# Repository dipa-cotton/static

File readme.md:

# static
custom FM Radio, with a SX1278 for LoRA capabilities!

## project overview
this FM radio contains a RDA5807, TDA2822, an infrared sensor, and a SX1278. these are the main components, and along with a 0.96 inch OLED display, a microSD card module, and more, this project is versatile and can both play audio as well as function as an FM radio, along with LORA capabilities.

## pictures

There was no CAD Case built for this project, so the case can be built later on once the antenna and potentiometer + button placement can be visualized. (I haven't decided on the button placement for this project yet, so I don't want to constrain placement just yet. Once it is assembled, a case will be built.)

## BOM Overview
- 3 10K ohm resistor
- 1 100 ohm resistor
- 5 polarized capacitors
- 1 4.7 µF decoupling capacitor
- 3 100nF capacitors
- 1 10nF capacitor
- 2 10pf capacitors
- 1 PJ-3200
- 1 0.96in OLED Display
- 1 MicroSD Card Module
- 2 speakers
- 2 potentiometers
- 4 push buttons
- 1 XIAO rp2040 microcontroller
- 1 RDA5807
- 1 TDA2822
- 1 TSOP38238
- 1 SX1278
- 1 32 MHz Crystal
### Overall cost: (including shipping and PCB) is $58

a more detailed list can be found in BOM.csv :)

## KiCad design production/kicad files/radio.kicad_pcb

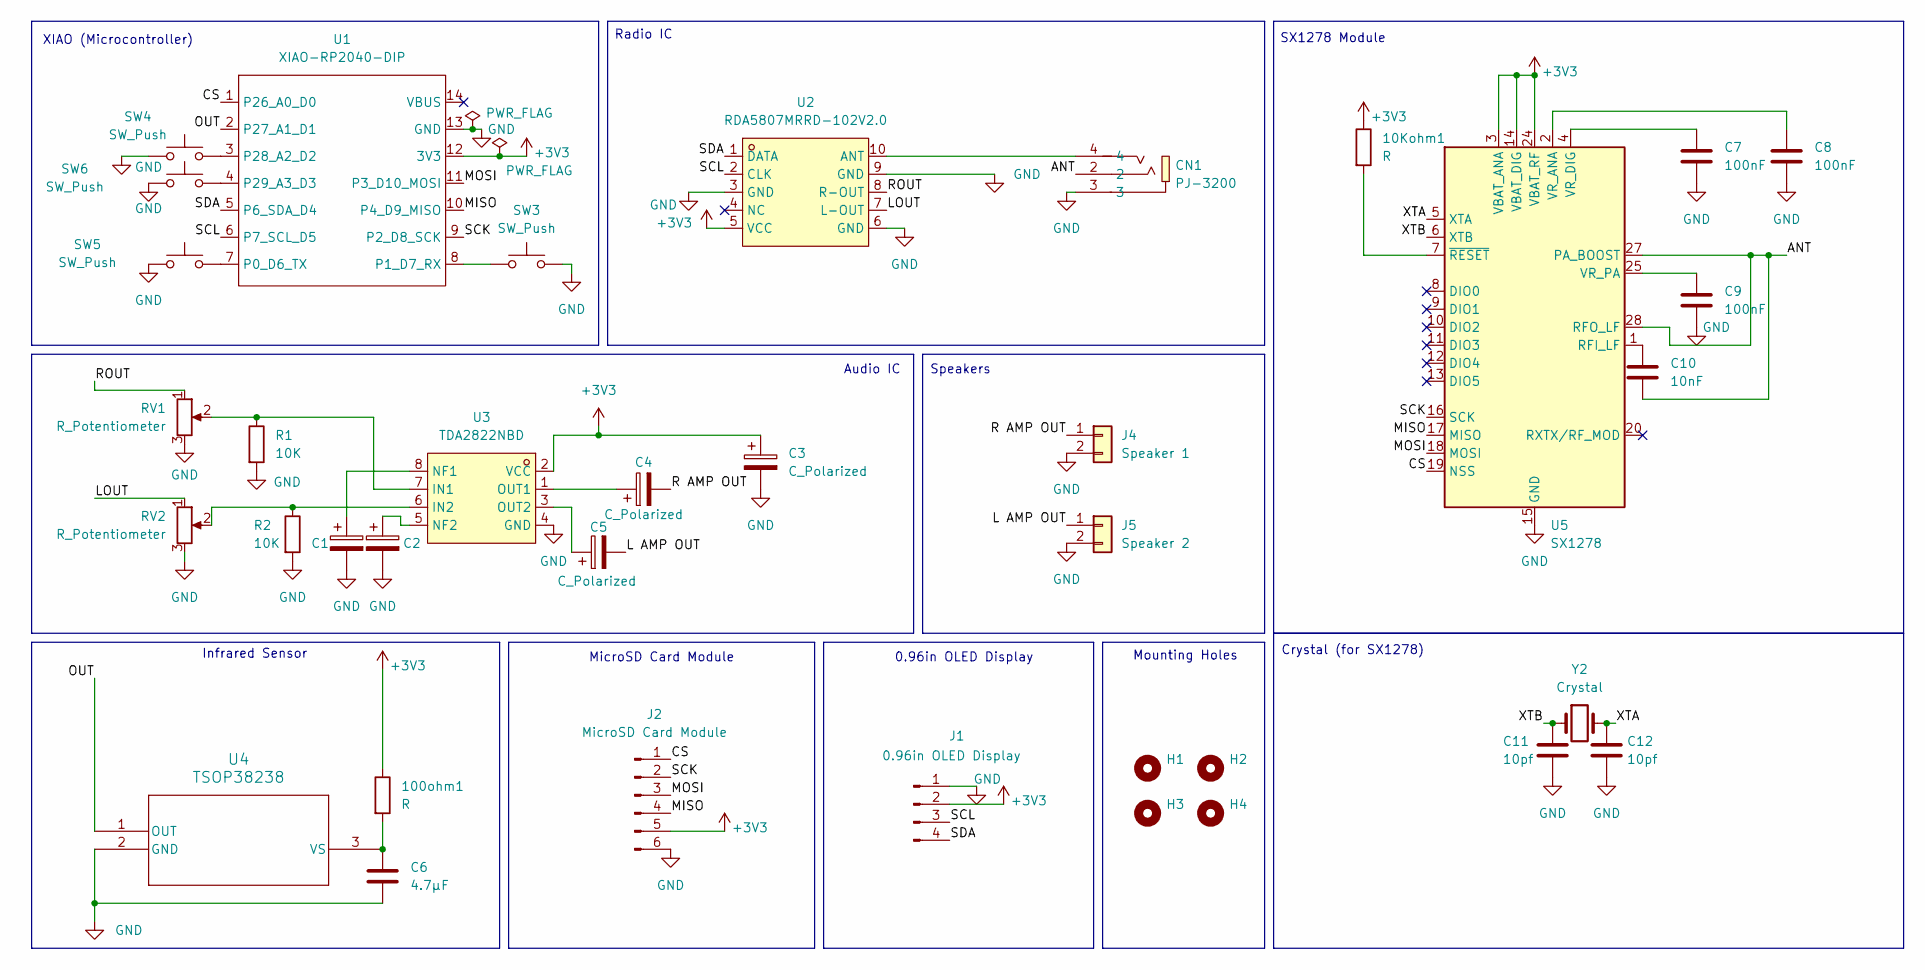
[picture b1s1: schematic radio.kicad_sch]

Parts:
10Kohm1, 100ohm1: R; R_Axial_DIN0204_L3.6mm_D1.6mm_P7.62mm_Horizontal
C1, C2, C3, C4, C5: C_Polarized; CP_Radial_D6.3mm_P2.50mm
C6: 4.7µF; R_Axial_DIN0204_L3.6mm_D1.6mm_P1.90mm_Vertical
C7, C8, C9: 100nF; R_Axial_DIN0204_L3.6mm_D1.6mm_P1.90mm_Vertical
C10: 10nF; R_Axial_DIN0204_L3.6mm_D1.6mm_P1.90mm_Vertical
C11, C12: 10pf; R_Axial_DIN0204_L3.6mm_D1.6mm_P1.90mm_Vertical
CN1: PJ-3200; AUDIO-TH_PJ-3200; MPN PJ-3200; LCSC Part C2689690
H1, H2, H3, H4: MountingHole; MountingHole_2.7mm_M2.5
J1: 0.96in OLED Display; PinHeader_1x04_P2.54mm_Vertical
J2: MicroSD Card Module; PinHeader_1x06_P2.54mm_Vertical
J4: Speaker 1; PinHeader_1x02_P2.54mm_Vertical
J5: Speaker 2; PinHeader_1x02_P2.54mm_Vertical
R1, R2: 10K; R_Axial_DIN0207_L6.3mm_D2.5mm_P7.62mm_Horizontal
RV1, RV2: R_Potentiometer; PinHeader_1x03_P2.54mm_Vertical
SW3, SW4, SW5, SW6: SW_Push; PinHeader_1x02_P2.54mm_Vertical
U1: XIAO-RP2040-DIP
U2: RDA5807MRRD-102V2.0; RDA5807; MPN RDA5807MRRD-102V2.0; LCSC Part C9900205627
U3: TDA2822NBD; DIP-8_W7.62mm; MPN TDA2822NBD; LCSC Part C51927337
U4: TSOP38238; TSOP382
U5: SX1278; QFN-28-1EP_6x6mm_P0.65mm_EP4.8x4.8mm
Y2: Crystal; Crystal_AT310_D3.0mm_L10.0mm_Horizontal

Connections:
+3V3: 10Kohm1.1, 100ohm1.1, C3.1, J1.2, J2.5, U1.12 (3V3), U2.5 (VCC), U3.2 (VCC), U5.3 (VBAT_ANA), U5.14 (VBAT_DIG), U5.24 (VBAT_RF)
/ANT: C10.2, CN1.2, U5.27 (PA_BOOST), U5.28 (RFO_LF)
/CS: J2.1, U1.1 (P26_A0_D0), U5.19 (NSS)
/L AMP OUT: C5.2, J5.1
/LOUT: RV2.1, U2.7 (L-OUT)
/MISO: J2.4, U1.10 (P4_D9_MISO), U5.17 (MISO)
/MOSI: J2.3, U1.11 (P3_D10_MOSI), U5.18 (MOSI)
/OUT: U1.2 (P27_A1_D1), U4.1 (OUT)
/R AMP OUT: C4.2, J4.1
/ROUT: RV1.1, U2.8 (R-OUT)
/SCK: J2.2, U1.9 (P2_D8_SCK), U5.16 (SCK)
/SCL: J1.3, U1.6 (P7_SCL_D5), U2.2 (CLK)
/SDA: J1.4, U1.5 (P6_SDA_D4), U2.1 (DATA)
/XTA: C12.1, U5.5 (XTA), Y2.2
/XTB: C11.1, U5.6 (XTB), Y2.1
GND: C1.2, C2.2, C3.2, C6.2, C7.2, C8.2, C9.2, C11.2, C12.2, CN1.3, J1.1, J2.6, J4.2, J5.2, R1.2, R2.2, RV1.3, RV2.3, SW3.2, SW4.1, SW5.1, SW6.1, U1.13 (GND), U2.3 (GND), U2.6 (GND), U2.9 (GND), U3.4 (GND), U4.2 (GND), U5.15 (GND), U5.21 (GND), U5.22 (GND), U5.23 (GND), U5.26 (GND), U5.29 (GND)
unnamed: SW5.2, U1.7 (P0_D6_TX)
unnamed: SW3.1, U1.8 (P1_D7_RX)
unnamed: SW4.2, U1.3 (P28_A2_D2)
unnamed: SW6.2, U1.4 (P29_A3_D3)
unnamed: CN1.4, U2.10 (ANT)
unnamed: R1.1, RV1.2, U3.7 (IN1)
unnamed: R2.1, RV2.2, U3.6 (IN2)
unnamed: C1.1, U3.8 (NF1)
unnamed: C2.1, U3.5 (NF2)
unnamed: C4.1, U3.1 (OUT1)
unnamed: C5.1, U3.3 (OUT2)
unnamed: 100ohm1.2, C6.1, U4.3 (VS)
unnamed: C10.1, U5.1 (RFI_LF)
unnamed: C8.1, U5.2 (VR_ANA)
unnamed: C7.1, U5.4 (VR_DIG)
unnamed: C9.1, U5.25 (VR_PA)
unnamed: 10Kohm1.2, U5.7 (~RESET)

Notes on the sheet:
MicroSD Card Module
SX1278 Module
Audio IC
Infrared Sensor
Mounting Holes
Radio IC
XIAO (Microcontroller)
Crystal (for SX1278)
0.96in OLED Display
Speakers

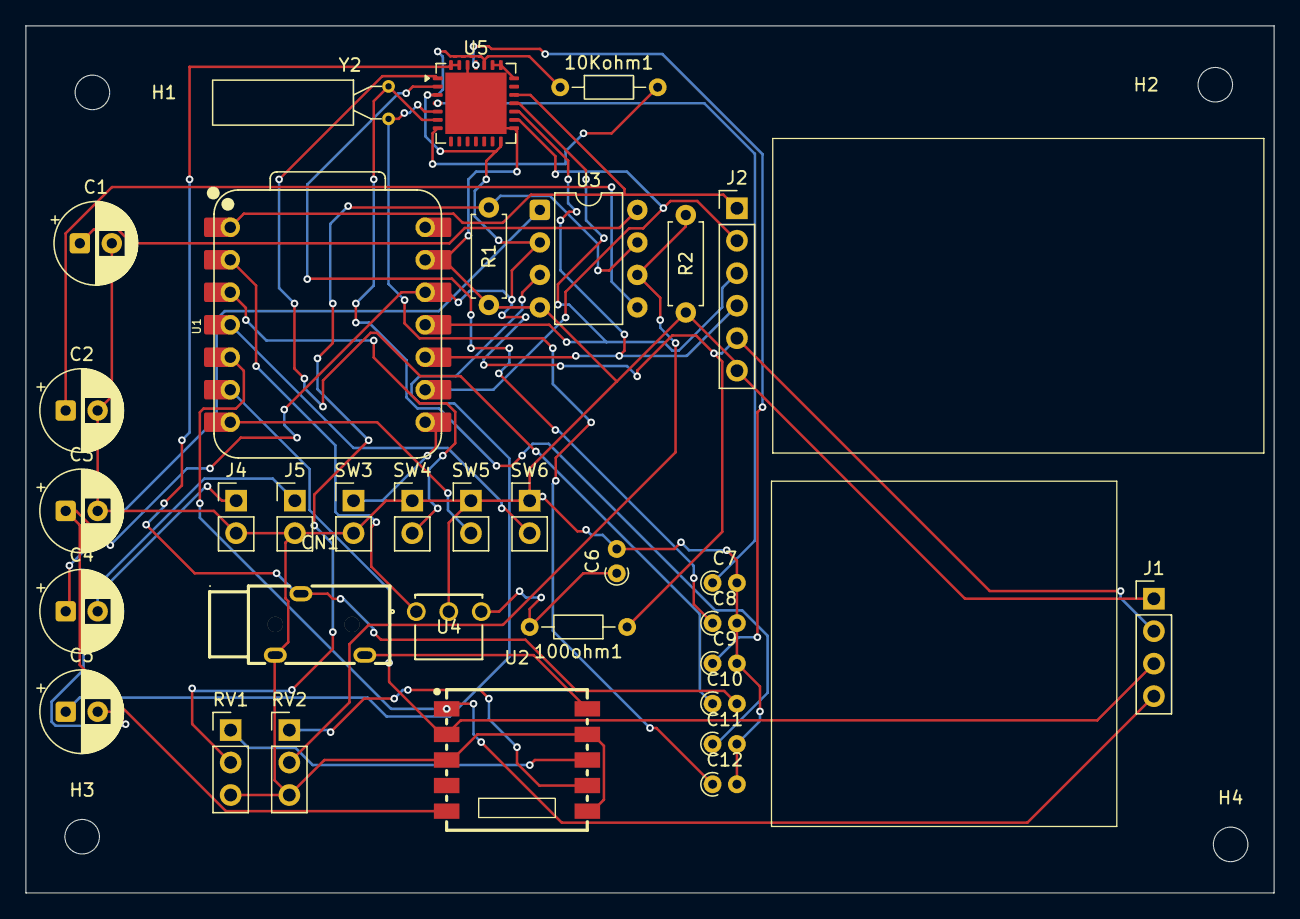
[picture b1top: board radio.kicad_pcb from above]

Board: 2 copper layers, 97.6 x 67.8 mm, 37 parts (0 on the bottom side), 33 nets.
